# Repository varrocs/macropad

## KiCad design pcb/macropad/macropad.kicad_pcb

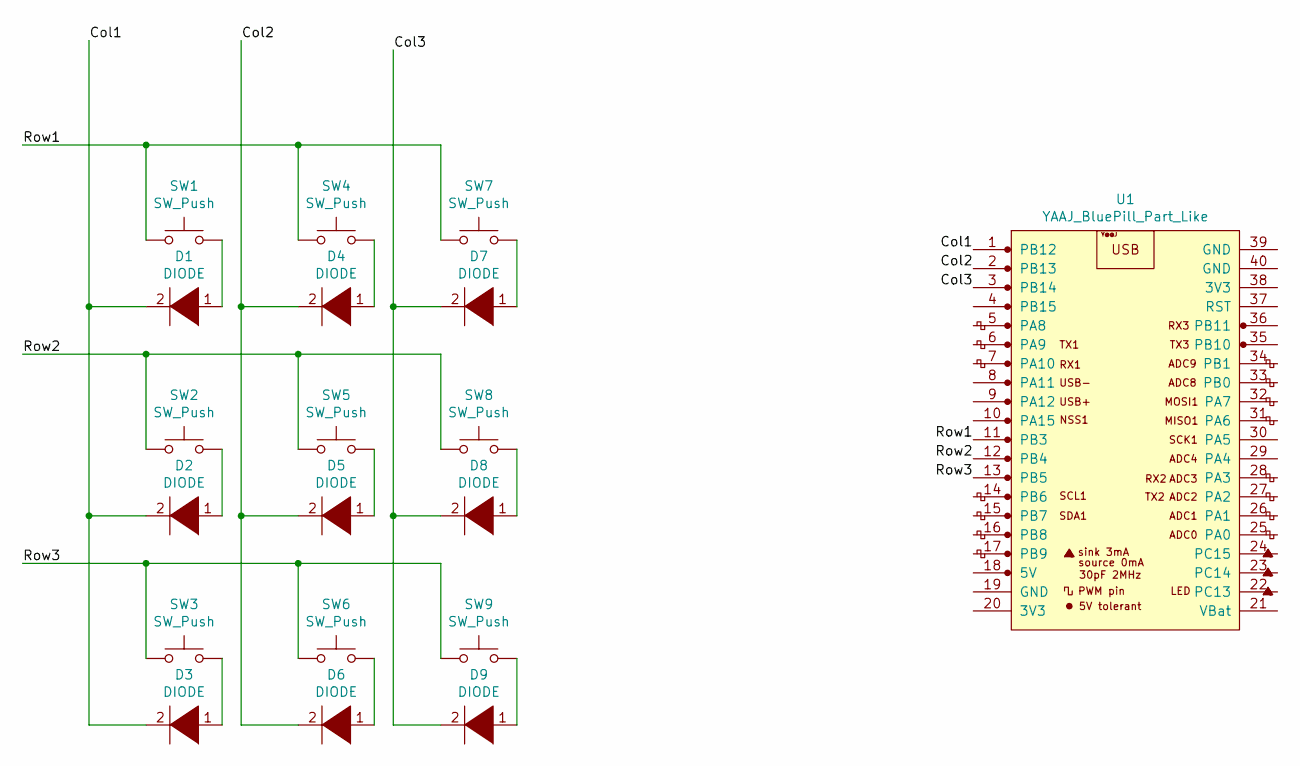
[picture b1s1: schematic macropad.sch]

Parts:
D1, D2, D3, D4, D5, D6, D7, D8, D9: DIODE; D_SOD-123
SW1, SW2, SW3, SW4, SW5, SW6, SW7, SW8, SW9: SW_Push; SW_Cherry_MX_1.00u_PCB
U1: YAAJ_BluePill_Part_Like; YAAJ_BluePill_1

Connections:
/Col1: D1.2 (A), D2.2 (A), D3.2 (A), U1.1 (PB12)
/Col2: D4.2 (A), D5.2 (A), D6.2 (A), U1.2 (PB13)
/Col3: D7.2 (A), D8.2 (A), D9.2 (A), U1.3 (PB14)
/Row1: SW1.1, SW4.1, SW7.1, U1.11 (PB3)
/Row2: SW2.1, SW5.1, SW8.1, U1.12 (PB4)
/Row3: SW3.1, SW6.1, SW9.1, U1.13 (PB5)
unnamed: D1.1 (K), SW1.2
unnamed: D2.1 (K), SW2.2
unnamed: D3.1 (K), SW3.2
unnamed: D4.1 (K), SW4.2
unnamed: D5.1 (K), SW5.2
unnamed: D6.1 (K), SW6.2
unnamed: D7.1 (K), SW7.2
unnamed: D8.1 (K), SW8.2
unnamed: D9.1 (K), SW9.2

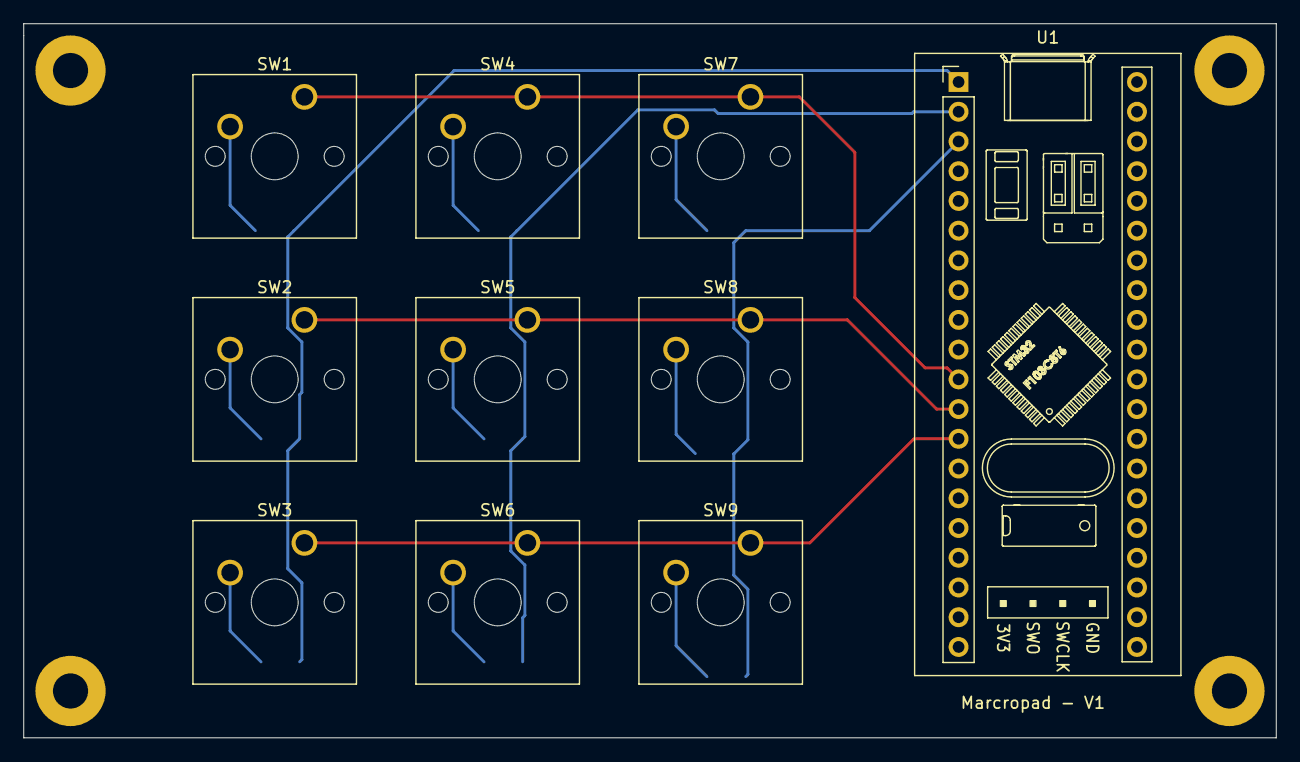
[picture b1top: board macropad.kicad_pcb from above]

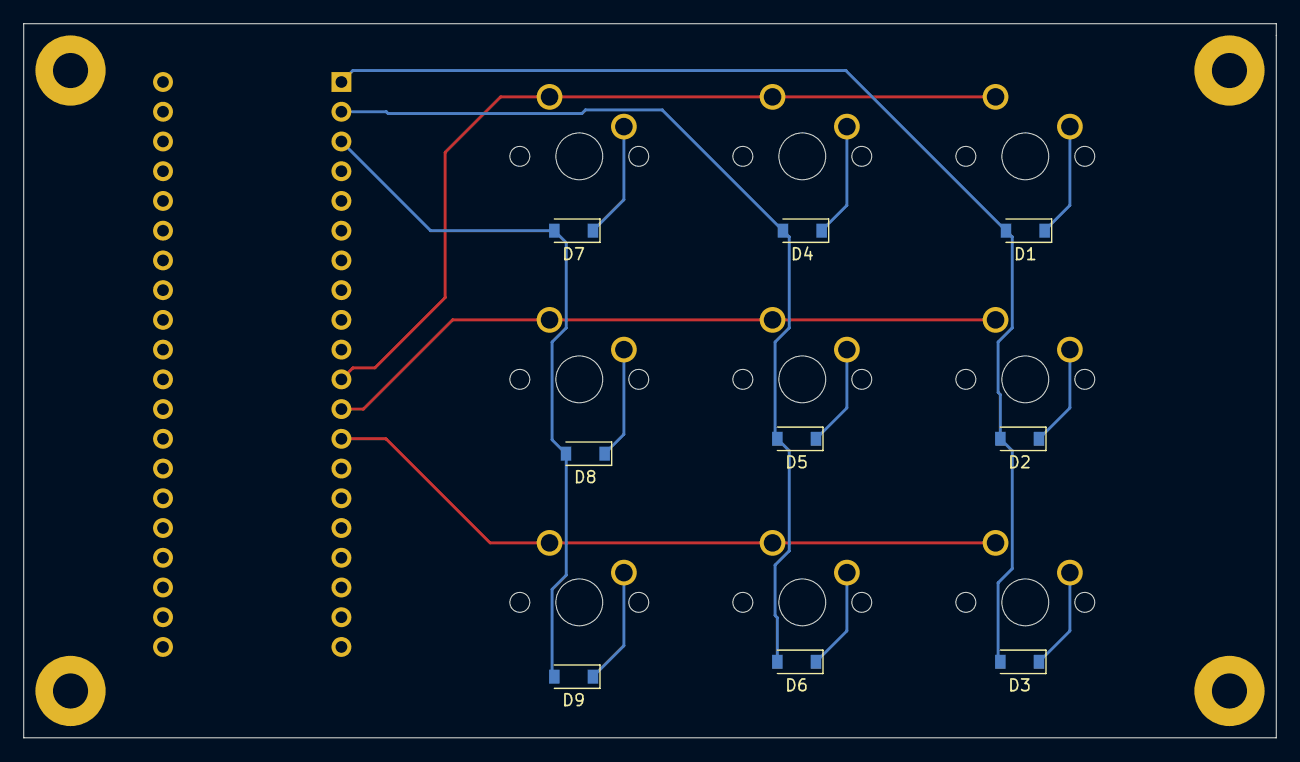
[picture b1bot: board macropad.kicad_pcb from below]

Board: 2 copper layers, 107.0 x 61.0 mm, 19 parts (9 on the bottom side), 15 nets.

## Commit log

2021-01-23 Add pcb
2021-01-23 Firmware
2021-01-26 Add shell
2021-01-28 Split main.c to multiple files
2021-01-29 Key press through command line works
2021-01-31 Shell works and looks okay
2021-02-02 More file separation. echo based commanding works
2021-02-04 Keystroke sequences can be set
2021-02-05 More ERR/OK error messages
2021-02-08 In refactor
2021-02-11 After char->keypress refactor. 2 byte scancodes (modifier+actual scancode) are stored instead of a simlpe ascii character
2021-02-12 Use generated ASCII <-> SCANCODE tables
2021-02-13 scancode to ascii fix; retry pressed keys if those failed
2021-02-13 Scancode based sequeces are working
2021-02-17 Add matrix scanning
2022-11-21 add macropad-daemon
2022-11-21 I don't know what is this
